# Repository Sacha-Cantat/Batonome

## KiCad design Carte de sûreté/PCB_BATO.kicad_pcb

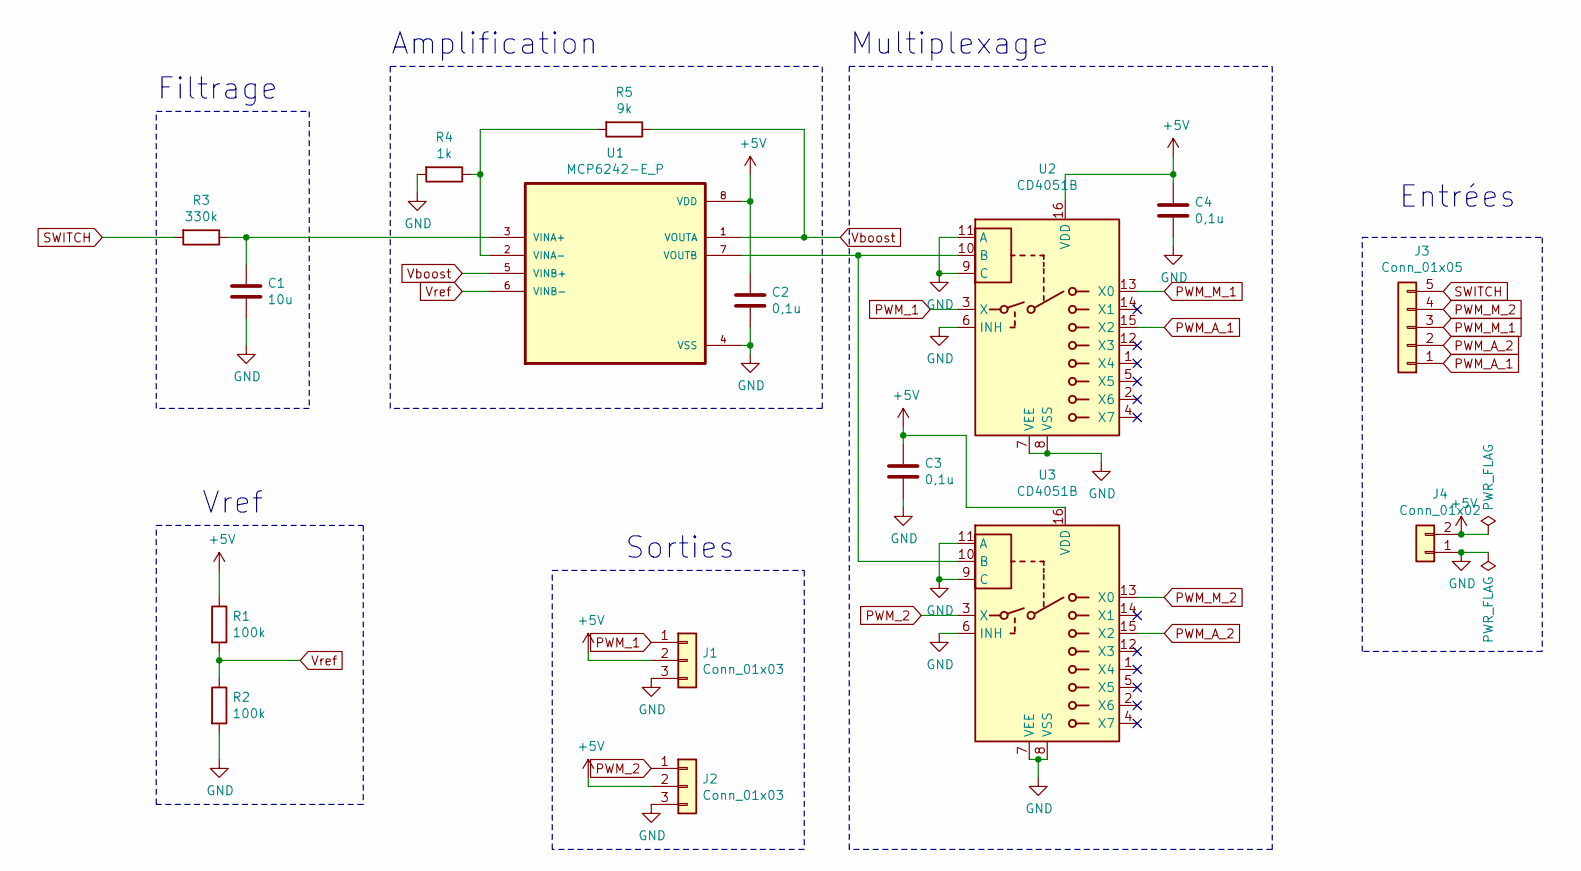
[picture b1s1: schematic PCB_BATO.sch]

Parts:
C1: 10u; C_Radial_D6.3mm_H7.0mm_P2.50mm
C2, C3, C4: 0,1u; C_Disc_D5.0mm_W2.5mm_P2.50mm
J1, J2: Conn_01x03; TerminalBlock_Phoenix_MKDS-1,5-3-5.08_1x03_P5.08mm_Horizont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
J3: Conn_01x05; TerminalBlock_Phoenix_MKDS-1,5-5-5.08_1x05_P5.08mm_Horizont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
J4: Conn_01x02; TerminalBlock_Phoenix_MKDS-1,5-2-5.08_1x02_P5.08mm_Horizont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
R1, R2: 100k; R_Axial_DIN0207_L6.3mm_D2.5mm_P15.24mm_Horizontal
R3: 330k; R_Axial_DIN0207_L6.3mm_D2.5mm_P15.24mm_Horizontal
R4: 1k; R_Axial_DIN0207_L6.3mm_D2.5mm_P15.24mm_Horizontal
R5: 9k; R_Axial_DIN0207_L6.3mm_D2.5mm_P15.24mm_Horizontal
U1: MCP6242-E_P; DIP787W46P254L927H533Q8
U2, U3: CD4051B; DIP794W45P254L1969H508Q16

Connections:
+5V: C2.1, C3.1, C4.1, J1.2, J2.2, J4.2, R1.1, U1.8 (VDD), U2.16 (VDD), U3.16 (VDD)
GND: C1.2, C2.2, C3.2, C4.2, J1.3, J2.3, J4.1, R2.2, R4.2, U1.4 (VSS), U2.6 (INH), U2.7 (VEE), U2.8 (VSS), U2.9 (C), U2.11 (A), U3.6 (INH), U3.7 (VEE), U3.8 (VSS), U3.9 (C), U3.11 (A)
unnamed: C1.1, R3.1, U1.3 (VINA+)
unnamed: R4.1, R5.2, U1.2 (VINA-)
unnamed: U1.7 (VOUTB), U2.10 (B), U3.10 (B)
PWM_1: J1.1, U2.3 (X)
PWM_2: J2.1, U3.3 (X)
PWM_A_1: J3.1, U2.15 (X2)
PWM_A_2: J3.2, U3.15 (X2)
PWM_M_1: J3.3, U2.13 (X0)
PWM_M_2: J3.4, U3.13 (X0)
SWITCH: J3.5, R3.2
Vboost: R5.1, U1.1 (VOUTA), U1.5 (VINB+)
Vref: R1.2, R2.1, U1.6 (VINB-)

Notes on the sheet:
Filtrage
Amplification
Multiplexage
Entrées
Sorties
Vref

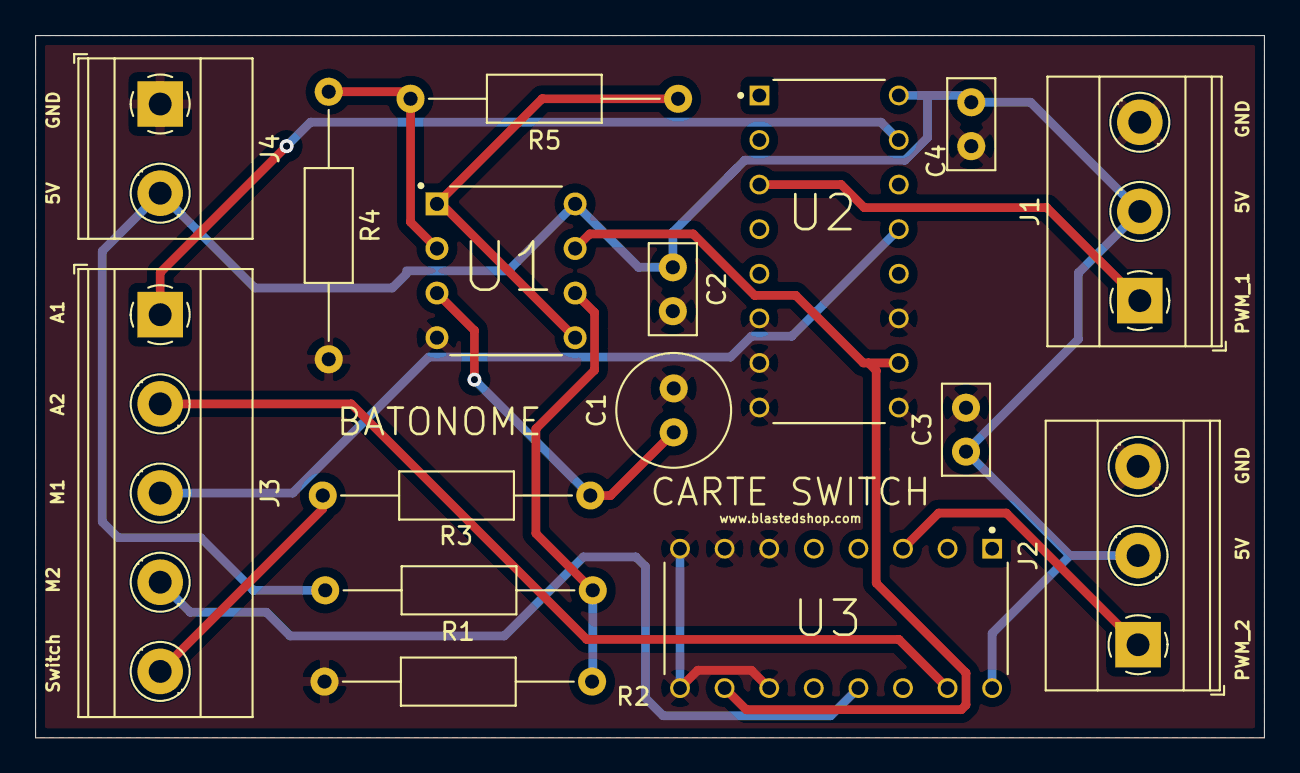
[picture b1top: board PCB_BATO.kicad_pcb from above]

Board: 2 copper layers, 70.0 x 40.0 mm, 16 parts (0 on the bottom side), 14 nets.

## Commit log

2022-11-29 Update the name of the repo
2022-12-13 Application Graphique Batonome
2022-12-13 Document de spécification projet
2022-12-13 Projet CUBEMX Batonome
2022-12-14 IHM Retour d'info Batonome et init de la zone de navigation
2022-12-14 Plus nécéssaire
2022-12-14 Click de la sourie enregistre le point GPS dans un tuple
2022-12-14 passage de l'appli sous Ctkinter
2022-12-14 Changement d'état du bouton d'init Zone en fonction du process
2022-12-15 Ajout bouton Balise
2022-12-15 Saisie des infos GPS de la balise
2022-12-16 Image cadenas sur le bouton setZone
2022-12-16 Image cadena sur bouton balise
2022-12-16 Enregistrement des coorodonés de la balise dans un tuple
2022-12-16 Une fois la zone de nav ok, on peut init la balise avec un clic souris
2022-12-16 Affichage
2023-01-04 Ajout barre de navigation sur la gauche
2023-01-05 Implementation bouton connect
2023-01-05 Maj Cube MX
2023-01-05 gitignore
2023-01-05 Modif vitesse com uart1
2023-01-05 Ajout fichier Zigbee
2023-01-05 Creation tache zigbee
2023-01-05 Uart 2 gps
2023-01-06 Lancement de la tâche IMU managment
2023-01-10 Zigbee
2023-01-10 Modif soft
2023-01-10 merge
2023-01-10 Reception it zigbee
2023-01-10 Maj projet
2023-01-10 Projet nettoyé
2023-01-12 Uart en extern
2023-01-12 Ajout config i2C
2023-01-12 fix gitignore
2023-01-12 remove old folder
2023-01-12 improve git ignore
2023-01-16 Switch to C++
2023-01-16 fix last commit issue
2023-01-16 change name
2023-01-17 Ajout zigbee communication PC
2023-01-19 Emission serie toutes les secondes
2023-01-21 Implémentation decodage trame série
2023-01-27 Bateau recois information GPS depuis GUI
2023-02-02 We can set at max 10 GPS coord for the nav zone
2023-03-05 Ajout PWM
2023-03-05 Ahout des fichier de config gestionPWM
2023-03-07 Gestion de la dérive fonctionnelle
2023-03-07 Gestion de la derive par les touche du clavier
2023-03-14 Commmande via PC ok
2023-03-15 Debut travaux GPS
2023-03-15 Angle du vent
2023-03-21 Mise a jour GPS
2023-05-11 Calib
2023-05-11 Tache navigation
2023-05-25 Girouette ok
2023-05-25 IMU ok !
2023-05-25 Ouverture au publique
2023-05-26 Fichier carte de sûreté
2023-05-26 STL Girouette
2023-06-10 Livraison finale
